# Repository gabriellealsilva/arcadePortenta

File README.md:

# Arcade Portenta
Personal project to try to replicate an arcade machine CPS-1 using bare-metal C++ on an Arduino Portenta H7(STM32H747XI)

The main goal is to build a retro arcade machine that can emulate the CPS-1 and run Street Fighter II at its native speed. The system will read and load a ROM from an SD card, and the players will interact with it using  JAMMA controllers. The output will be done using VGA for a CRT monitor and most likely I2S for the audio.

## Where to look
- `AGENTS.md` — project goal, repository map, architecture, build commands and conventions (written for humans and AI agents alike)
- `STATUS.md` — what is done and what is left
- `Hardware/CarrierPCB/` — KiCad project of the carrier board

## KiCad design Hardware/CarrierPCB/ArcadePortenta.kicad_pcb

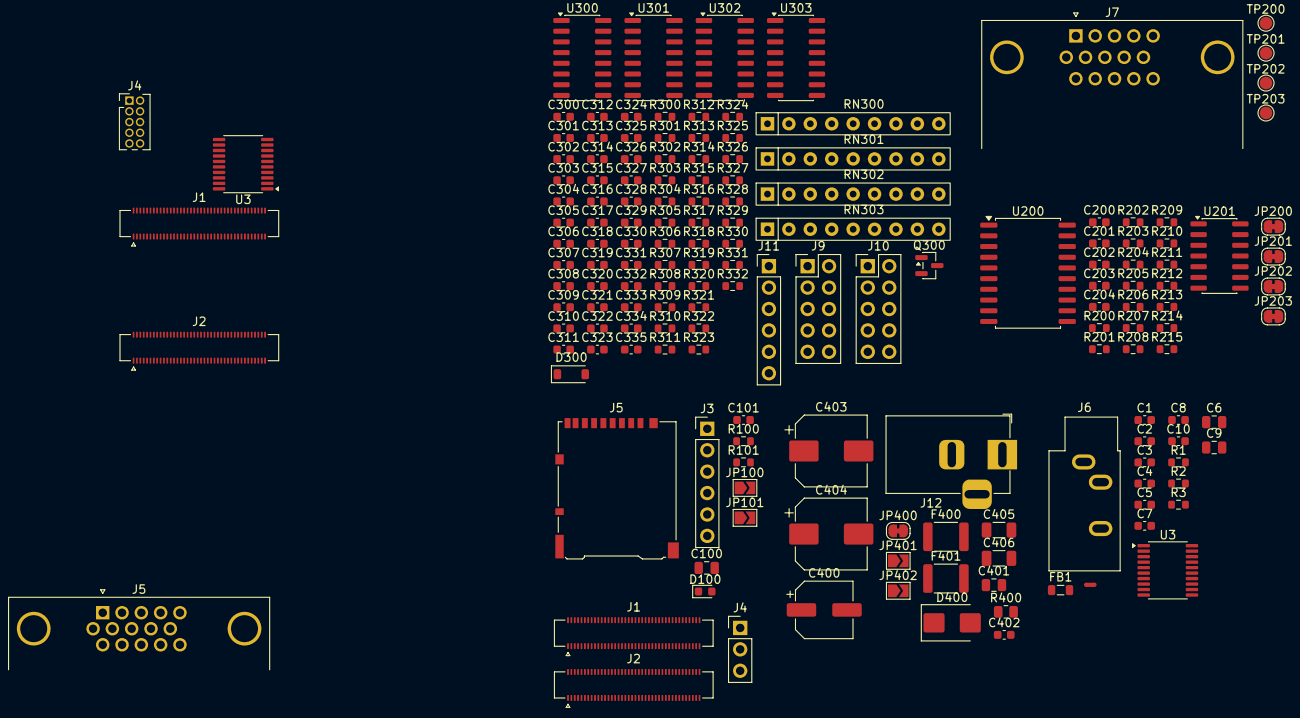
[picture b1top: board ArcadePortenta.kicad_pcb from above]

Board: 2 copper layers, 163 parts (0 on the bottom side), 125 nets, no tracks yet.

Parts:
C1, C2, C3: 2.2uF; C_0603_1608Metric
C4, C5: 2.2nF; C_0603_1608Metric
C6, C9, C100, C401: 10uF; C_0805_2012Metric
C7, C8, C10, C101, C203, C204, C300, C301, C302, C303, C304, C305, C306, C307, C308, C309, C310, C311, C312, C313, C314, C315, C316, C317, C318, C319, C320, C321, C322, C323, C324, C325, C326, C327, C328, C329, C330, C331, C332, C333, C334, C335, C402: 100nF; C_0603_1608Metric
C200, C201, C202: 22pF; C_0603_1608Metric
C400: 100uF; CP_Elec_6.3x7.7
C403, C404: 220uF; CP_Elec_8x10
C405: 10uF; C_1206_3216Metric
C406: 10nF/250V; C_1206_3216Metric
D100: LED; LED_0603_1608Metric
D300: 1N4148W; D_SOD-123
D400: SMBJ5.0A; D_SMB
F400, F401: 2A; Fuse_1812_4532Metric
FB1: 600R@100MHz; L_0805_2012Metric
J1: PORTENTA_J1; Hirose_DF40HC(3.5)-80DS-0.4V_2x40_P0.4mm
J1#2, J2#2: Conn_02x40_Counter_Clockwise; Hirose_DF40HC(3.5)-80DS-0.4V_2x40_P0.4mm
J2: PORTENTA_J2; Hirose_DF40HC(3.5)-80DS-0.4V_2x40_P0.4mm
J3: SWD; PinHeader_1x06_P2.54mm_Vertical
J4: Conn_ARM_JTAG_SWD_10; PinHeader_2x05_P1.27mm_Vertical
J4#2: UART-DEBUG; PinHeader_1x03_P2.54mm_Vertical
J5: DA15_Pins_MountingHoles; DSUB-15-HD_Pins_Horizontal_P2.29x1.90mm_EdgePinOffset3.03mm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
J5#2: microSD; microSD_HC_Hirose_DM3AT-SF-PEJM5
J6: LINE-OUT; Jack_3.5mm_CUI_SJ1-3533NG_Horizontal
J7: VGA; DSUB-15-HD_Pins_Horizontal_P2.29x2.54mm_EdgePinOffset8.35mm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
J9: KICK-P1; PinHeader_2x05_P2.54mm_Vertical
J10: KICK-P2; PinHeader_2x05_P2.54mm_Vertical
J11: AUX; PinHeader_1x06_P2.54mm_Vertical
J12: 5V-DC; BarrelJack_Horizontal
JP100: VSD-3V3; SolderJumper-2_P1.3mm_Open_TrianglePad1.0x1.5mm
JP101: MODE 31k/15k; SolderJumper-2_P1.3mm_Open_TrianglePad1.0x1.5mm
JP200: JAMMA_R; SolderJumper-2_P1.3mm_Bridged_RoundedPad1.0x1.5mm
JP201: JAMMA_G; SolderJumper-2_P1.3mm_Bridged_RoundedPad1.0x1.5mm
JP202: JAMMA_B; SolderJumper-2_P1.3mm_Bridged_RoundedPad1.0x1.5mm
JP203: JAMMA_SYNC; SolderJumper-2_P1.3mm_Bridged_RoundedPad1.0x1.5mm
JP400: BARREL-5V; SolderJumper-2_P1.3mm_Bridged_RoundedPad1.0x1.5mm
JP401: JAMMA-5V; SolderJumper-2_P1.3mm_Open_TrianglePad1.0x1.5mm
JP402: EARTH-BOND; SolderJumper-2_P1.3mm_Open_TrianglePad1.0x1.5mm
NT1: NetTie_2; NetTie-2_SMD_Pad0.5mm
Q300: MMBT2222A; SOT-23
R1, R2: 470; R_0603_1608Metric
R3, R100: 10k; R_0603_1608Metric
R101: 330; R_0603_1608Metric
R200, R211: 536; R_0603_1608Metric
R201, R212: 1.07k; R_0603_1608Metric
R202, R213: 2.15k; R_0603_1608Metric
R203, R214: 4.32k; R_0603_1608Metric
R204, R215: 8.66k; R_0603_1608Metric
R205: 549; R_0603_1608Metric
R206: 1.1k; R_0603_1608Metric
R207: 2.21k; R_0603_1608Metric
R208: 4.42k; R_0603_1608Metric
R209: 8.87k; R_0603_1608Metric
R210: 17.8k; R_0603_1608Metric
R300, R301, R302, R303, R304, R305, R306, R307, R308, R309, R310, R311, R312, R313, R314, R315, R316, R317, R318, R319, R320, R321, R322, R323, R324, R325, R326, R327, R328, R329, R330, R331, R332: 1k; R_0603_1608Metric
R400: 1M; R_0805_2012Metric
RN300, RN301, RN302, RN303: 10k; R_Array_SIP9
TP200: PCLK; TestPoint_Pad_D1.5mm
TP201: HSYNC; TestPoint_Pad_D1.5mm
TP202: VSYNC; TestPoint_Pad_D1.5mm
TP203: CSYNC; TestPoint_Pad_D1.5mm
U3, U3#2: PCM5102A; TSSOP-20_4.4x6.5mm_P0.65mm
U200: 74HCT244; SOIC-20W_7.5x12.8mm_P1.27mm
U201: 74HC86; SOIC-14_3.9x8.7mm_P1.27mm
U300, U301, U302, U303: 74HC165; SOIC-16_3.9x9.9mm_P1.27mm

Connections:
+3.3V: C6.1, C7.1, C8.1, C308.1, C317.1, C326.1, C335.1, FB1.1, J2.23, J2.34, J2.43, J2.69, J3.1, J4.1 (VTref), JP100.2 (B), R100.1, RN300.1 (common), RN301.1 (common), RN302.1 (common), RN303.1 (common), U3.1 (CPVDD), U3.20 (DVDD), U3#2.20 (DVDD), U300.16 (VCC), U301.16 (VCC), U302.16 (VCC), U303.16 (VCC)
+3.3VA: C9.1, C10.1, FB1.2, U3.8 (AVDD), U3#2.1 (CPVDD)
+5V: C203.1, C204.1, C400.1, C401.1, C402.1, J1.21, J1.32, J1.41, J1.48, JP400.2 (B), JP401.2 (B), U200.20 (VCC), U201.14 (VCC)
/Portenta/led_k: D100.2 (A), R101.2
/SCK: J1#2.56, U3#2.13 (BCK)
/SDO: J1#2.62, U3#2.14 (DIN)
/WS: J1#2.58, U3#2.15 (LRCK)
/audio/capm: C1.2, U3.4 (CAPM)
/audio/capp: C1.1, U3.2 (CAPP)
/audio/ldoo: C3.1, U3.18 (LDOO)
/audio/outl: R1.1, U3.6 (OUTL)
/audio/outr: R2.1, U3.7 (OUTR)
/audio/vneg: C2.1, U3.5 (VNEG)
/inputs/cnt_b: Q300.1 (B), R300.2
/inputs/n_0_0: C300.1, R301.2, RN300.2 (R1), U300.11 (D0)
/inputs/n_0_1: C301.1, R302.2, RN300.3 (R2), U300.12 (D1)
/inputs/n_0_2: C302.1, R303.2, RN300.4 (R3), U300.13 (D2)
/inputs/n_0_3: C303.1, R304.2, RN300.5 (R4), U300.14 (D3)
/inputs/n_0_4: C304.1, R305.2, RN300.6 (R5), U300.3 (D4)
/inputs/n_0_5: C305.1, R306.2, RN300.7 (R6), U300.4 (D5)
/inputs/n_0_6: C306.1, R307.2, RN300.8 (R7), U300.5 (D6)
/inputs/n_0_7: C307.1, R308.2, RN300.9 (R8), U300.6 (D7)
/inputs/n_1_0: C309.1, R309.2, RN301.2 (R1), U301.11 (D0)
/inputs/n_1_1: C310.1, R310.2, RN301.3 (R2), U301.12 (D1)
/inputs/n_1_2: C311.1, R311.2, RN301.4 (R3), U301.13 (D2)
/inputs/n_1_3: C312.1, R312.2, RN301.5 (R4), U301.14 (D3)
/inputs/n_1_4: C313.1, R313.2, RN301.6 (R5), U301.3 (D4)
/inputs/n_1_5: C314.1, R314.2, RN301.7 (R6), U301.4 (D5)
/inputs/n_1_6: C315.1, R315.2, RN301.8 (R7), U301.5 (D6)
/inputs/n_1_7: C316.1, R316.2, RN301.9 (R8), U301.6 (D7)
/inputs/n_2_0: C318.1, R317.2, RN302.2 (R1), U302.11 (D0)
/inputs/n_2_1: C319.1, R318.2, RN302.3 (R2), U302.12 (D1)
/inputs/n_2_2: C320.1, R319.2, RN302.4 (R3), U302.13 (D2)
/inputs/n_2_3: C321.1, R320.2, RN302.5 (R4), U302.14 (D3)
/inputs/n_2_4: C322.1, R321.2, RN302.6 (R5), U302.3 (D4)
/inputs/n_2_5: C323.1, R322.2, RN302.7 (R6), U302.4 (D5)
/inputs/n_2_6: C324.1, R323.2, RN302.8 (R7), U302.5 (D6)
/inputs/n_2_7: C325.1, R324.2, RN302.9 (R8), U302.6 (D7)
/inputs/n_3_0: C327.1, R325.2, RN303.2 (R1), U303.11 (D0)
/inputs/n_3_1: C328.1, R326.2, RN303.3 (R2), U303.12 (D1)
/inputs/n_3_2: C329.1, R327.2, RN303.4 (R3), U303.13 (D2)
/inputs/n_3_3: C330.1, R328.2, RN303.5 (R4), U303.14 (D3)
/inputs/n_3_4: C331.1, R329.2, RN303.6 (R5), U303.3 (D4)
/inputs/n_3_5: C332.1, R330.2, RN303.7 (R6), U303.4 (D5)
/inputs/n_3_6: C333.1, R331.2, RN303.8 (R7), U303.5 (D6)
/inputs/n_3_7: C334.1, R332.2, RN303.9 (R8), U303.6 (D7)
/power/v5_prot: D400.1 (A1), F400.2, JP400.1 (A)
/power/v12_amp: C404.1, C405.1
/power/v12_f: C403.1, F401.2
/power/vin_raw: F400.1, J12.1
CH1: U300.9 (Q7), U301.10 (DS)
CH2: U301.9 (Q7), U302.10 (DS)
CH3: U302.9 (Q7), U303.10 (DS)
CHASSIS: C406.1, J5#2.SH (SHIELD), J7.SH, JP402.1 (A), R400.1
COIN_CNT: J2.54, R300.1
COIN_CNT_OUT: D300.2 (A), Q300.3 (C)
CSYNC: JP203.1 (A), TP203.1 (1_1), U201.3
DBG_RX: J1.35, J4#2.2
DBG_TX: J1.33, J4#2.1
GND: C2.2, C3.2, C6.2, C7.2, C8.2, C100.2, C101.2, C200.2, C201.2, C202.2, C203.2, C204.2, C300.2, C301.2, C302.2, C303.2, C304.2, C305.2, C306.2, C307.2, C308.2, C309.2, C310.2, C311.2, C312.2, C313.2, C314.2, C315.2, C316.2, C317.2, C318.2, C319.2, C320.2, C321.2, C322.2, C323.2, C324.2, C325.2, C326.2, C327.2, C328.2, C329.2, C330.2, C331.2, C332.2, C333.2, C334.2, C335.2, C400.2, C401.2, C402.2, C403.2, C404.2, C405.2, C406.2, D100.1 (K), D400.2 (A2), J1.22, J1.31, J1.42, J1.47, J1.54, J2.24, J2.33, J2.44, J2.57, J2.70, J3.5, J4.3 (GND), J4.5 (GND), J4.9 (GNDDetect), J4#2.3, J5#2.6 (VSS), J5#2.10 (DET_A), J7.5, J7.6, J7.7, J7.8, J7.10, J9.2, J9.4, J9.6, J9.8, J9.10, J10.2, J10.4, J10.6, J10.8, J10.10, J11.6, J12.2, J12.3, JP101.2 (B), JP402.2 (B), NT1.1, Q300.2 (E), R3.2, R400.2, U3.3 (CPGND), U3.10 (DEMP), U3.11 (FLT), U3.12 (SCK), U3.16 (FMT), U3.19 (DGND), U3#2.10 (DEMP), U3#2.11 (FLT), U3#2.12 (SCK), U3#2.16 (FMT), U3#2.19 (DGND), U200.1 (OEa), U200.6 (I2a), U200.8 (I3a), U200.10 (GND), U200.11 (I0b), U200.13 (I1b), U200.15 (I2b), U200.17 (I3b), U200.19 (OEb), U201.4, U201.5, U201.7 (GND), U201.9, U201.10, U201.12, U201.13, U300.8 (GND), U300.10 (DS), U300.15 (~CE), U301.8 (GND), U301.15 (~CE), U302.8 (GND), U302.15 (~CE), U303.8 (GND), U303.15 (~CE)
GNDA: C4.2, C5.2, C9.2, C10.2, J6.S, NT1.2, U3.9 (AGND), U3#2.3 (CPGND), U3#2.9 (AGND)
HSYNC: J2.61, TP201.1 (1_1), U200.2 (I0a)
HSYNC_5V: J7.13, U200.18 (O0a), U201.1
I2S_CK: J1.56, U3.13 (BCK)
I2S_SDO: J1.62, U3.14 (DIN)
I2S_WS: J1.58, U3.15 (LRCK)
IN_AUX1: J11.1, R328.1
IN_AUX2: J11.2, R329.1
IN_AUX3: J11.3, R330.1
IN_AUX4: J11.4, R331.1
IN_AUX5: J11.5, R332.1
IN_CLK: J2.40, U300.2 (CP), U301.2 (CP), U302.2 (CP), U303.2 (CP)
IN_DATA: J2.42, U303.9 (Q7)
IN_LATCH: J1.34, U300.1 (~PL), U301.1 (~PL), U302.1 (~PL), U303.1 (~PL)
IN_P1B4: J9.1, R308.1
IN_P1B5: J9.3, R309.1
IN_P1B6: J9.5, R310.1
IN_P2B4: J10.1, R318.1
IN_P2B5: J10.3, R319.1
IN_P2B6: J10.5, R320.1
JAMMA_12V: D300.1 (K), F401.1
LC: C4.1, J6.T, R1.2
LED_STAT: J2.48, R101.1
LTDC_B3: J2.59, R215.1
LTDC_B4: J2.6, R214.1
LTDC_B5: J2.18, R213.1
LTDC_B6: J2.4, R212.1
LTDC_B7: J2.2, R211.1
LTDC_G2: J2.27, R210.1
LTDC_G3: J2.66, R209.1
LTDC_G4: J2.67, R208.1
LTDC_G5: J2.36, R207.1
LTDC_G6: J2.60, R206.1
LTDC_G7: J1.60, R205.1
LTDC_R3: J2.16, R204.1
LTDC_R4: J2.14, R203.1
LTDC_R5: J2.12, R202.1
LTDC_R6: J2.10, R201.1
LTDC_R7: J1.29, R200.1
MODE_JP: J2.56, JP101.1 (A)
NRST: J1.73, J3.4
PCLK: J2.65, TP200.1 (1_1)
RC: C5.1, J6.R, R2.2
SD_CD: J2.46, J5#2.9 (DET_B), R100.2
SD_CLK: J1.55, J5#2.5 (CLK)
SD_CMD: J1.57, J5#2.3 (CMD)
SD_D0: J1.59, J5#2.7 (DAT0)
SD_D1: J1.61, J5#2.8 (DAT1)
SD_D2: J1.63, J5#2.1 (DAT2)
SD_D3: J1.65, J5#2.2 (DAT3/CD)
SWCLK: J1.77, J3.3
SWDIO: J1.75, J3.2
TCK/SCK: J1#2.77, J4.4 (SWCLK/TCK)
TDI: J1#2.74, J4.8 (NC/TDI)
TDO/SWO: J1#2.79, J4.6 (SWO/TDO)
TMS/SWD: J1#2.75, J4.2 (SWDIO/TMS)
VDDA: U3#2.8 (AVDD), U3#2.17 (XSMT)
VID_B: C202.1, J7.3, JP202.1 (A), R211.2, R212.2, R213.2, R214.2, R215.2
VID_G: C201.1, J7.2, JP201.1 (A), R205.2, R206.2, R207.2, R208.2, R209.2, R210.2
VID_R: C200.1, J7.1, JP200.1 (A), R200.2, R201.2, R202.2, R203.2, R204.2
VSD: C100.1, C101.1, J1.74, J5#2.4 (VDD), JP100.1 (A)
VSYNC: J2.22, TP202.1 (1_1), U200.4 (I1a)
VSYNC_5V: J7.14, U200.16 (O1a), U201.2
XSMT: J2.50, R3.1, U3.17 (XSMT)
/RESET: J1#2.73, J4.10 (~RESET)

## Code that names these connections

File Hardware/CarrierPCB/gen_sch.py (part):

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  - power.kicad_sch    (new: 5V/12V entry, protection, chassis tie)
  - ArcadePortenta.kicad_sch (root: add two sheet blocks)
  - audio.kicad_sch    (patched in place: global I2S labels, bead, net-tie,
                        jack, XSMT, strap pins)
Connectivity is done with labels and power symbols placed exactly on pin
connection points; only decorative short wires are drawn.
"""
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 9:(NC,""), 11:(NC,""), 13:(NC,""), 15:(NC,""), 17:(NC,"ETH_L1"),
 19:(NC,"ETH_L2"), 21:(PW,"+5V"), 23:(NC,"USB1_VBUS"), 25:(NC,"USB1_D+"),
 27:(NC,"USB1_D-"), 29:(GL,"LTDC_R7"), 31:(PW,"GND"), 33:(GL,"DBG_TX"),
 35:(GL,"DBG_RX"), 37:(NC,"PI14"), 39:(NC,"PI15"), 41:(PW,"+5V"),
 43:(NC,"PB7-PMIC"), 45:(NC,"PB6-PMIC"), 47:(PW,"GND"), 49:(NC,"PH13"),
 51:(NC,"PB8"), 53:(NC,"VSYS"), 55:(GL,"SD_CLK"), 57:(GL,"SD_CMD"),
 59:(GL,"SD_D0"), 61:(GL,"SD_D1"), 63:(GL,"SD_D2"), 65:(GL,"SD_D3"),
 67:(NC,""), 69:(NC,""), 71:(NC,""), 73:(GL,"NRST"), 75:(GL,"SWDIO"),
 77:(GL,"SWCLK"), 79:(NC,"SWO=PB3"),
 2:(NC,""), 4:(NC,""), 6:(NC,""), 8:(NC,""), 10:(NC,"DSI"), 12:(NC,"DSI"),
 14:(NC,"DSI"), 16:(NC,"DSI"), 18:(NC,"DSI"), 20:(NC,"DSI"), 22:(PW,"GND"),
 24:(NC,""), 26:(NC,"USB0_D+"), 28:(NC,"USB0_D-"), 30:(NC,""),
 32:(PW,"+5V"), 34:(GL,"IN_LATCH"), 36:(NC,"PI9"), 38:(NC,"PI10"),
 40:(NC,"PI13"), 42:(PW,"GND"), 44:(NC,"PH8"), 46:(NC,"PH7"),
 48:(PW,"+5V"), 50:(NC,""), 52:(NC,""), 54:(PW,"GND"), 56:(GL,"I2S_CK"),
 58:(GL,"I2S_WS"), 60:(GL,"LTDC_G7"), 62:(GL,"I2S_SDO"), 64:(NC,"VSYS"),
 66:(NC,""), 68:(NC,""), 70:(NC,"PE2"), 72:(NC,"PB2"), 74:(GL,"VSD"),
 76:(NC,""), 78:(NC,""), 80:(NC,""),
}
J2 = {
 1:(NC,""), 3:(NC,""), 5:(NC,""), 7:(NC,"COINCELL"), 9:(NC,""), 11:(NC,""),
 13:(NC,""), 15:(NC,""), 17:(NC,""), 19:(NC,""), 21:(NC,""),
 23:(PW,"+3.3V"), 25:(NC,"PJ8"), 27:(GL,"LTDC_G2"), 29:(NC,""), 31:(NC,""),
 33:(PW,"GND"), 35:(NC,""), 37:(NC,""), 39:(NC,""), 41:(NC,""),
 43:(PW,"+3.3V"), 45:(NC,"PH12*"), 47:(NC,"PH11*"), 49:(NC,"PI5*"),
 51:(NC,"PI7*"), 53:(NC,"PI6*"), 55:(NC,""), 57:(PW,"GND"),
 59:(GL,"LTDC_B3"), 61:(GL,"HSYNC"), 63:(NC,"PC7"), 65:(GL,"PCLK"),
 67:(GL,"LTDC_G4"), 69:(PW,"+3.3V"), 71:(NC,"VREF+"), 73:(NC,"PA0*"),
 75:(NC,"PA1"), 77:(NC,"A2"), 79:(NC,"A3"),
 2:(GL,"LTDC_B7"), 4:(GL,"LTDC_B6"), 6:(GL,"LTDC_B4"), 8:(NC,"PH14"),
 10:(GL,"LTDC_R6"), 12:(GL,"LTDC_R5"), 14:(GL,"LTDC_R4"), 16:(GL,"LTDC_R3"),
 18:(GL,"LTDC_B5"), 20:(NC,"PA6"), 22:(GL,"VSYNC"), 24:(PW,"GND"),
 26:(NC,"PG14"), 28:(NC,"PG9"), 30:(NC,""), 32:(NC,""), 34:(PW,"+3.3V"),
 36:(GL,"LTDC_G5"), 38:(NC,"PI1"), 40:(GL,"IN_CLK"), 42:(GL,"IN_DATA"),
 44:(PW,"GND"), 46:(GL,"SD_CD"), 48:(GL,"LED_STAT"), 50:(GL,"XSMT"),
 52:(NC,"PD5-amp"), 54:(GL,"COIN_CNT"), 56:(GL,"MODE_JP"), 58:(NC,"PG10"),
 60:(GL,"LTDC_G6"), 62:(NC,"PH15"), 64:(NC,"PJ7"), 66:(GL,"LTDC_G3"),
 68:(NC,"PH6"), 70:(PW,"GND"), 72:(NC,"VREF-"), 74:(NC,"PC2*"),
 76:(NC,"PC3*"), 78:(NC,"PA4*"), 80:(NC,"PA6*"),
}
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            "Arduino_PortentaBreakout lib and STM32H747XIH6 CubeMX DB.\\n"
            "Pads marked Px* share an MCU ball with another pad (dual bond) - "
            "twin left NC:\\n"
            "  PB3 = J1-63 (SD_D2) = J1-79 (SWO): SWO unavailable.\\n"
            "  PA0 = J1-34 (IN_LATCH) = J2-73 (A0).  PA4 = J2-22 (VSYNC) = J2-78.\\n"
            "  PC2 = J2-40 = J2-74.  PC3 = J2-42 = J2-76.  PH11 = J2-12 = J2-47.\\n"
            "  PH12 = J2-10 = J2-45.  PI5 = J2-18 = J2-49.  PI6 = J2-4 = J2-53.  "
            "PI7 = J2-2 = J2-51.\\n"
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        if sig[0] == "pw": sh.pwr(sig[1], x, y)
        elif sig[0] == "gl": sh.glabel(sig[1], x, y, 0)
        else: sh.nc(x, y)
    sh.note("SWO not available (PB3 used as SD_D2)", 280, 52)

    # Debug UART header J4
    w = sh.place("Connector_Generic", "Conn_01x03", "J4", "UART-DEBUG",
                 285, 70, "Connector_PinHeader_2.54mm:PinHeader_1x03_P2.54mm_Vertical")
    sh.glabel("DBG_TX", *w["1"][:2], 0)
    sh.glabel("DBG_RX", *w["2"][:2], 0)
    sh.pwr("GND", *w["3"][:2])

    # microSD socket J5 on SDMMC2
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    # SD_CD pull-up + VSD decoupling
    w = sh.place("Device", "R", "R100", "10k", 330, 165,
                 "Resistor_SMD:R_0603_1608Metric")
    sh.glabel("SD_CD", *w["2"][:2], 90); sh.pwr("+3.3V", *w["1"][:2])
    w = sh.place("Device", "C", "C100", "10uF", 345, 165,
                 "Capacitor_SMD:C_0805_2012Metric")
    sh.glabel("VSD", *w["1"][:2], 90); sh.pwr("GND", *w["2"][:2])
    w = sh.place("Device", "C", "C101", "100nF", 355, 165,
                 "Capacitor_SMD:C_0603_1608Metric")
    sh.glabel("VSD", *w["1"][:2], 90); sh.pwr("GND", *w["2"][:2])
    w = sh.place("Jumper", "SolderJumper_2_Open", "JP100", "VSD-3V3", 345, 180,
                 "Jumper:SolderJumper-2_P1.3mm_Open_TrianglePad1.0x1.5mm", dnp=True)
    sh.glabel("VSD", *w["1"][:2], 180); sh.pwr("+3.3V", *w["2"][:2])
    sh.note("VSD: module V-SDCARD pad feeds SD socket VDD.\\n"
            "Close JP100 only if V-SDCARD turns out not to source 3V3 "
            "(verify against Portenta schematic before closing!)", 320, 195)
    sh.flag(365, 165); sh.glabel("VSD", 365, 165, 0)

    # status LED
    w = sh.place("Device", "R", "R101", "330", 285, 95,
                 "Resistor_SMD:R_0603_1608Metric")
    sh.glabel("LED_STAT", *w["1"][:2], 90)
    rbot = w["2"][:2]
    w = sh.place("Device", "LED", "D100", "LED", 285, 107,
                 "LED_SMD:LED_0603_1608Metric")
    # connect R bottom to LED top via labels
    sh.llabel("led_k", *rbot, 0); sh.llabel("led_k", *w["2"][:2], 0)
    sh.pwr("GND", *w["1"][:2])

    # video mode jumper (PG3): open = VGA 31k, closed = CRT 15k
    w = sh.place("Jumper", "SolderJumper_2_Open", "JP101", "MODE 31k/15k",
                 285, 125, "Jumper:SolderJumper-2_P1.3mm_Open_TrianglePad1.0x1.5mm")
    sh.glabel("MODE_JP", *w["1"][:2], 180)
    sh.pwr("GND", *w["2"][:2])
    sh.note("PG3 mode select: open = VGA 640x480@60 (31.5 kHz),\\n"
            "closed = CRT 384x224@59.6 (15.6 kHz). Firmware pull-up.", 275, 135)
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                 "Package_SO:SOIC-20W_7.5x12.8mm_P1.27mm")
    sh.pwr("GND", *w["1"][:2])                     # OEa
    sh.pwr("GND", *w["19"][:2])                    # OEb
    sh.glabel("HSYNC", *w["2"][:2], 180)
    sh.glabel("VSYNC", *w["4"][:2], 180)
    sh.glabel("HSYNC_5V", *w["18"][:2], 0)
    sh.glabel("VSYNC_5V", *w["16"][:2], 0)
    for pin in ("6", "8", "11", "13", "15", "17"): sh.pwr("GND", *w[pin][:2])
    for pin in ("14", "12", "9", "7", "5", "3"):   sh.nc(*w[pin][:2])
    sh.pwr("+5V", *w["20"][:2]); sh.pwr("GND", *w["10"][:2])
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    # CSYNC = HSYNC_5V xor VSYNC_5V - 74HC86 @5V (fed by 5V CMOS outputs)
    w = sh.place("74xx", "74LS86", "U201", "74HC86", 280, 60,
                 "Package_SO:SOIC-14_3.9x8.7mm_P1.27mm", unit=1)
    sh.glabel("HSYNC_5V", *w["1"][:2], 180)
    sh.glabel("VSYNC_5V", *w["2"][:2], 180)
    sh.glabel("CSYNC", *w["3"][:2], 0)
    for u, pins in ((2, ("4", "5")), (3, ("9", "10")), (4, ("12", "13"))):
        w = sh.place("74xx", "74LS86", "U201", "74HC86", 280, 60 + u * 25, unit=u)
        for p in pins: sh.pwr("GND", *w[p][:2])
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        else: sh.nc(x, y)
    if "SH" in w:
        x, y, ang = w["SH"]
        sh.glabel("CHASSIS", x, y, 270)
    sh.note("DDC (pins 12/15) unused. Pin 9 (+5V key) NC.", 345, 130)

    # JAMMA video takeoff jumpers
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    # coin counter driver (DNP)
    w = sh.place("Transistor_BJT", "MMBT2222A", "Q300", "MMBT2222A", 110, 220,
                 "Package_TO_SOT_SMD:SOT-23", dnp=True)
    sh.glabel("COIN_CNT_OUT", *w["3"][:2], 90)    # collector (top)
    sh.pwr("GND", *w["2"][:2])                    # emitter (bottom)
    base = w["1"][:2]
    w = sh.place("Device", "R", "R300", "1k", 95, 220,
                 "Resistor_SMD:R_0603_1608Metric", dnp=True)
    sh.llabel("cnt_b", *w["2"][:2], 0); sh.llabel("cnt_b", *base, 0)
    sh.glabel("COIN_CNT", *w["1"][:2], 90)
    w = sh.place("Device", "D", "D300", "1N4148W", 130, 220,
                 "Diode_SMD:D_SOD-123", dnp=True)
    sh.glabel("JAMMA_12V", *w["1"][:2], 180)
    sh.glabel("COIN_CNT_OUT", *w["2"][:2], 0)
    sh.note("Coin counter (DNP): PE3 -> Q300 low-side, flyback to +12V "
            "(counter coil supply).", 90, 235)

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        for bi in range(8):
            sh.llabel("n_%d_%d" % (ci, bi), *wn[str(bi + 2)][:2], 0)
        # control pins
        sh.glabel("IN_LATCH", *w["1"][:2], 180)     # SH/LD
        sh.glabel("IN_CLK",   *w["2"][:2], 180)     # CLK
        sh.pwr("GND", *w["15"][:2])                 # CLK INH
        if ci == 0:
            sh.pwr("GND", *w["10"][:2])             # SER of first chip
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        if ci < 3:
            sh.glabel("CH%d" % (ci + 1), *w["9"][:2], 0)   # QH -> next SER
        else:
            sh.glabel("IN_DATA", *w["9"][:2], 0)           # QH -> MCU
        sh.nc(*w["7"][:2])                          # /QH
        sh.pwr("+3.3V", *w["16"][:2]); sh.pwr("GND", *w["8"][:2])
        wc = sh.place("Device", "C", "C%d" % cn, "100nF", ux + 30, uy + 25,
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            "point only; open when JAMMA PSU already bonds earth).", 15, 20, 1.5)
    w = sh.place("Connector", "Barrel_Jack_Switch", "J12", "5V-DC", 40, 60,
                 "Connector_BarrelJack:BarrelJack_Horizontal")
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
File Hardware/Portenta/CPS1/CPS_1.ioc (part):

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Mcu.Name=STM32H747XIHx
Mcu.Package=TFBGA240
Mcu.UserName=STM32H747XIHx
PA0.GPIOParameters=GPIO_Label
PA0.GPIO_Label=IN165_LATCH
PA0.PinAttribute=CortexM7
PA0.Signal=GPIO_Output
PA4.GPIOParameters=PinAttribute
PA4.Mode=RGB565
PA4.PinAttribute=CortexM7
PA4.Signal=LTDC_VSYNC
PA8.GPIOParameters=PinAttribute
PA8.Mode=RGB565
PA8.PinAttribute=CortexM7
PA8.Signal=LTDC_B3
PA9.GPIOParameters=PinAttribute
PA9.Mode=Asynchronous
PA9.PinAttribute=CortexM7
PA9.Signal=USART1_TX
PA10.GPIOParameters=PinAttribute
PA10.Mode=Asynchronous
PA10.PinAttribute=CortexM7
PA10.Signal=USART1_RX
PA13\ (JTMS/SWDIO).GPIOParameters=PinAttribute
PA13\ (JTMS/SWDIO).Mode=Serial_Wire
PA13\ (JTMS/SWDIO).PinAttribute=CortexM7
PA13\ (JTMS/SWDIO).Signal=DEBUG_JTMS-SWDIO
PA14\ (JTCK/SWCLK).GPIOParameters=PinAttribute
PA14\ (JTCK/SWCLK).Mode=Serial_Wire
PA14\ (JTCK/SWCLK).PinAttribute=CortexM7
PA14\ (JTCK/SWCLK).Signal=DEBUG_JTCK-SWCLK
PB2.GPIOParameters=PinAttribute
PB2.Mode=Single Bank 1
PB2.PinAttribute=CortexM7
PB2.Signal=QUADSPI_CLK
PB3\ (JTDO/TRACESWO).GPIOParameters=PinAttribute
PB3\ (JTDO/TRACESWO).Mode=SD_4_bits_Wide_bus
PB3\ (JTDO/TRACESWO).PinAttribute=CortexM7
PB3\ (JTDO/TRACESWO).Signal=SDMMC2_D2
PB4\ (NJTRST).GPIOParameters=PinAttribute
PB4\ (NJTRST).Mode=SD_4_bits_Wide_bus
PB4\ (NJTRST).PinAttribute=CortexM7
PB4\ (NJTRST).Signal=SDMMC2_D3
PB9.GPIOParameters=PinAttribute
PB9.Mode=Half_Duplex_Master_Tx
PB9.PinAttribute=CortexM4
PB9.Signal=I2S2_WS
PB14.GPIOParameters=PinAttribute
PB14.Mode=SD_4_bits_Wide_bus
PB14.PinAttribute=CortexM7
PB14.Signal=SDMMC2_D0
PB15.GPIOParameters=PinAttribute
PB15.Mode=SD_4_bits_Wide_bus
PB15.PinAttribute=CortexM7
PB15.Signal=SDMMC2_D1
PC2.GPIOParameters=GPIO_Label
PC2.GPIO_Label=IN165_CLK
PC2.PinAttribute=CortexM7
PC2.Signal=GPIO_Output
PC3.GPIOParameters=GPIO_Label
PC3.GPIO_Label=IN165_DATA
PC3.PinAttribute=CortexM7
PC3.Signal=GPIO_Input
PC6.GPIOParameters=PinAttribute
PC6.Mode=RGB565
PC6.PinAttribute=CortexM7
PC6.Signal=LTDC_HSYNC
PC13.GPIOParameters=GPIO_PuPd,GPIO_Label
PC13.GPIO_Label=SD_CARD_DETECT
PC13.GPIO_PuPd=GPIO_PULLUP
PC13.PinAttribute=CortexM7
PC13.Signal=GPIO_Input
PC15-OSC32_OUT\ (OSC32_OUT).GPIOParameters=GPIO_Label
PC15-OSC32_OUT\ (OSC32_OUT).GPIO_Label=STATUS_LED
PC15-OSC32_OUT\ (OSC32_OUT).PinAttribute=CortexM7
PC15-OSC32_OUT\ (OSC32_OUT).Signal=GPIO_Output
PD3.GPIOParameters=PinAttribute
PD3.Mode=Half_Duplex_Master_Tx
PD3.PinAttribute=CortexM4
PD3.Signal=I2S2_CK
PD4.GPIOParameters=GPIO_Label
PD4.GPIO_Label=AUDIO_XSMT
PD4.PinAttribute=CortexM4
PD4.Signal=GPIO_Output
PD5.GPIOParameters=GPIO_Label
PD5.GPIO_Label=AMP_MUTE
PD5.PinAttribute=CortexM4
PD5.Signal=GPIO_Output
PD6.GPIOParameters=PinAttribute
PD6.Mode=SD_4_bits_Wide_bus
PD6.PinAttribute=CortexM7
PD6.Signal=SDMMC2_CK
PD7.GPIOParameters=PinAttribute
PD7.Mode=SD_4_bits_Wide_bus
PD7.PinAttribute=CortexM7
PD7.Signal=SDMMC2_CMD
PD11.GPIOParameters=PinAttribute
PD11.Mode=Single Bank 1
PD11.PinAttribute=CortexM7
PD11.Signal=QUADSPI_BK1_IO0
PD12.GPIOParameters=PinAttribute
PD12.Mode=Single Bank 1
PD12.PinAttribute=CortexM7
PD12.Signal=QUADSPI_BK1_IO1
PD13.GPIOParameters=PinAttribute
PD13.Mode=Single Bank 1
PD13.PinAttribute=CortexM7
PD13.Signal=QUADSPI_BK1_IO3
PE2.GPIOParameters=PinAttribute
PE2.Mode=Single Bank 1
PE2.PinAttribute=CortexM7
PE2.Signal=QUADSPI_BK1_IO2
PE3.GPIOParameters=GPIO_Label
PE3.GPIO_Label=COIN_CTR
PE3.PinAttribute=CortexM7
PE3.Signal=GPIO_Output
PG3.GPIOParameters=GPIO_PuPd,GPIO_Label
PG3.GPIO_Label=VIDEO_MODE_SEL
PG3.GPIO_PuPd=GPIO_PULLUP
PG3.PinAttribute=CortexM7
PG3.Signal=GPIO_Input
PG6.GPIOParameters=PinAttribute
PG6.Mode=Single Bank 1
PG6.PinAttribute=CortexM7
PG6.Signal=QUADSPI_BK1_NCS
PG7.GPIOParameters=PinAttribute
PG7.Mode=RGB565
PG7.PinAttribute=CortexM7
PG7.Signal=LTDC_CLK
PH9.GPIOParameters=PinAttribute
PH9.Mode=RGB565
PH9.PinAttribute=CortexM7
PH9.Signal=LTDC_R3
PH10.GPIOParameters=PinAttribute
PH10.Mode=RGB565
PH10.PinAttribute=CortexM7
PH10.Signal=LTDC_R4
PH11.GPIOParameters=PinAttribute
PH11.Mode=RGB565
PH11.PinAttribute=CortexM7
PH11.Signal=LTDC_R5
PH12.GPIOParameters=PinAttribute
PH12.Mode=RGB565
PH12.PinAttribute=CortexM7
PH12.Signal=LTDC_R6
PI0.GPIOParameters=PinAttribute
PI0.Mode=RGB565
PI0.PinAttribute=CortexM7
PI0.Signal=LTDC_G5
PI2.GPIOParameters=PinAttribute
PI2.Mode=RGB565
PI2.PinAttribute=CortexM7
PI2.Signal=LTDC_G7
PI3.GPIOParameters=PinAttribute
PI3.Mode=Half_Duplex_Master_Tx
PI3.PinAttribute=CortexM4
PI3.Signal=I2S2_SDO
PI4.GPIOParameters=PinAttribute
PI4.Mode=RGB565
PI4.PinAttribute=CortexM7
PI4.Signal=LTDC_B4
PI5.GPIOParameters=PinAttribute
PI5.Mode=RGB565
PI5.PinAttribute=CortexM7
PI5.Signal=LTDC_B5
PI6.GPIOParameters=PinAttribute
PI6.Mode=RGB565
PI6.PinAttribute=CortexM7
PI6.Signal=LTDC_B6
PI7.GPIOParameters=PinAttribute
PI7.Mode=RGB565
PI7.PinAttribute=CortexM7
PI7.Signal=LTDC_B7
PJ6.GPIOParameters=PinAttribute
PJ6.Mode=RGB565
PJ6.PinAttribute=CortexM7
PJ6.Signal=LTDC_R7
PJ9.GPIOParameters=PinAttribute
PJ9.Mode=RGB565
PJ9.PinAttribute=CortexM7
PJ9.Signal=LTDC_G2
PJ10.GPIOParameters=PinAttribute
PJ10.Mode=RGB565
PJ10.PinAttribute=CortexM7
PJ10.Signal=LTDC_G3
PJ11.GPIOParameters=PinAttribute
PJ11.Mode=RGB565
PJ11.PinAttribute=CortexM7
PJ11.Signal=LTDC_G4
PK1.GPIOParameters=PinAttribute
PK1.Mode=RGB565
PK1.PinAttribute=CortexM7
PK1.Signal=LTDC_G6
RCC.HSE_VALUE=25000000
RCC.HSEState=RCC_HSE_ON
RCC.SYSCLKFreq_VALUE=480000000
RCC.SYSCLKSource=RCC_SYSCLKSOURCE_PLLCLK
board=custom

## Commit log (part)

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2026-05-01 Cleanup main structure
2026-05-01 Branch to emulate a display
2026-05-05 clang format added and gitignore updated
2026-05-05 First implementation of menu
2026-05-13 Updated structures CmakeLists, CMakes and gitignore
2026-05-13 All merge problems solved
2026-05-14 Fixing broken merges
2026-05-14 Main cleanup
